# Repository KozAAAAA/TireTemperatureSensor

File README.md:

# TireTemperatureSensor
This is the STM32 board which sends the data collected from the IR Sensor through the CAN bus.

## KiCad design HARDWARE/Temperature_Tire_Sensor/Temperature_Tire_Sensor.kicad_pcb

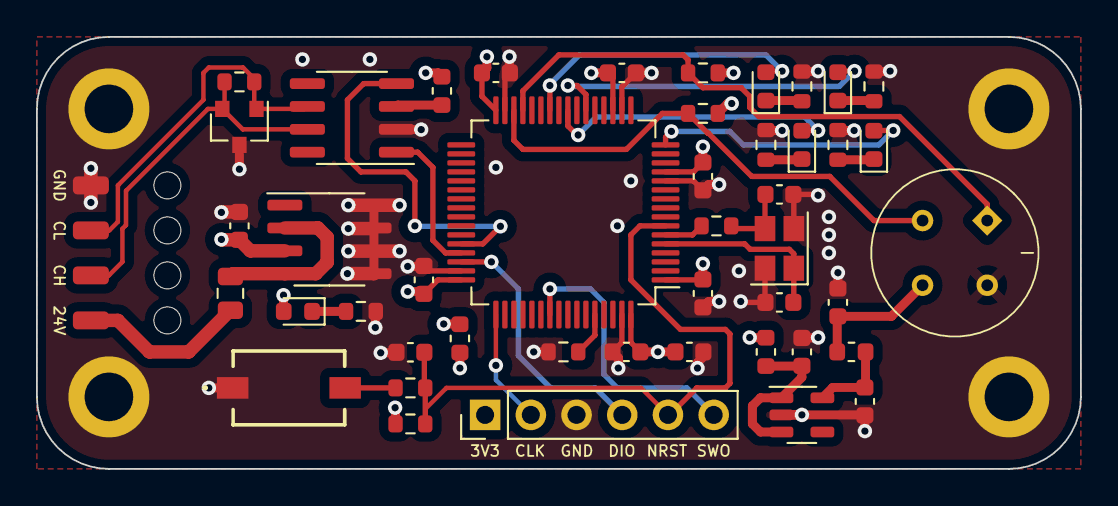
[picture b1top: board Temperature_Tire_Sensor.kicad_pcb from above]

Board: 4 copper layers, 58.0 x 24.0 mm, 50 parts (0 on the bottom side), 33 nets.

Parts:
C1: 0.1u; C_0603_1608Metric
C2: 4u7; C_0603_1608Metric
C3, C4, C6, C8, C9, C10, C11, C12, C14: 100n; C_0603_1608Metric
C5, C7: 8p; C_0603_1608Metric
C13: 10u <3.4Ohm; C_0603_1608Metric
D1, D6: RED; D_0603_1608Metric
D2: PESD2CAN,215; SOT-23
D3, D4: YELLOW; D_0603_1608Metric
D5: GREEN; D_0603_1608Metric
F1: Polyfuse; Fuse_0805_2012Metric
FB1, FB2, FB3, FB4: 60R@100MHz; L_0603_1608Metric
H1, H2, H3, H4: Mounting_Pad; MountingHole_2.7mm_M2.5_ISO14580_Pad
IC1: MLX90621ESF-BAB-000-SP; MLX90621ESFBAB000SP
J1: SWD_01x06; PinHeader_1x06_P2.54mm_Vertical
J2: CAN_01x04; SolderWirePad_1x04_SMD_1x2mm
R1: 100k; R_0603_1608Metric
R2, R8, R9, R11, R12: 1k5; R_0603_1608Metric
R3: 1k; R_0603_1608Metric
R4: 47; R_0603_1608Metric
R5, R6: 4k7; R_0603_1608Metric
R7: 120; R_0603_1608Metric
R10: 10k; R_0603_1608Metric
SW1: RESET; 434781025816
U1: STM32L4P5RET6; LQFP-64_10x10mm_P0.5mm
U2: MIC5236; SOIC-8_3.9x4.9mm_P1.27mm
U3: MIC5306-2.6YD5-TR; TSOT-23-5
U4: SN65HVD232; SOIC-8_3.9x4.9mm_P1.27mm
Y1: 16MGHz; Crystal_SMD_SeikoEpson_TSX3225-4Pin_3.2x2.5mm

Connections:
+2V6: C12.1, FB3.1, U3.5 (VOUT)
+3V3: C13.1, D6.2 (A), FB1.1, FB2.1, FB4.1, J1.1, R5.1, R6.1, R10.2, U2.3 (OUT)
+24V: F1.1, J2.1
/+3V3_uC: C2.1, C3.1, C4.1, C6.1, C8.1, C9.1, C10.1, FB1.2, U1.1 (VBAT), U1.13 (VDDA/VREF+), U1.19 (VDD), U1.32 (VDD), U1.48 (VDDUSB), U1.64 (VDD)
/CAN_H: D2.2 (K), J2.2, R7.1, U4.7 (CANH)
/CAN_L: D2.1 (K), J2.3, R7.2, U4.6 (CANL)
/CAN_RX: U1.44 (PA11), U4.4 (R)
/CAN_TX: U1.45 (PA12), U4.1 (D)
/LED_ERR: D1.2 (A), U1.22 (PA6)
/LED_OK: D5.2 (A), U1.26 (PB0)
/LED_WAR1: D3.2 (A), U1.24 (PC4)
/LED_WAR2: D4.2 (A), U1.16 (PA2)
/NRST: C1.1, J1.5, R3.2, R10.1, U1.7 (NRST)
/OSC_IN: C5.1, U1.5 (PH0-OSC_IN), Y1.1
/OSC_OUT: R4.1, U1.6 (PH1-OSC_OUT)
/SCL: IC1.1 (SCL), R6.2, U1.29 (PB10)
/SDA: IC1.2 (SDA), R5.2, U1.30 (PB11)
/SWCLK: J1.2, U1.49 (PA14)
/SWDIO: J1.4, U1.46 (PA13)
/SWO: J1.6, U1.55 (PB3)
GND: C1.2, C2.2, C3.2, C4.2, C5.2, C6.2, C7.2, C8.2, C9.2, C10.2, C11.2, C12.2, C13.2, C14.2, D2.3 (A), H1.1, H2.1, H3.1, H4.1, IC1.4 (GND), J1.3, J2.4, R1.2, R2.2, R8.2, R9.2, R11.2, R12.2, SW1.1, U1.12 (VSSA/VREF-), U1.18 (VSS), U1.31 (VSS), U1.47 (VSS), U1.63 (VSS), U2.5 (GND), U2.6 (GND), U2.7 (GND), U2.8 (GND), U3.2 (GND), U4.2 (GND), Y1.2, Y1.4
unnamed: C7.1, R4.2, Y1.3
unnamed: C11.1, FB2.2, U3.1 (VIN), U3.3 (EN)
unnamed: C14.1, FB3.2, IC1.3 (VDD)
unnamed: D1.1 (K), R2.1
unnamed: D3.1 (K), R8.1
unnamed: D4.1 (K), R9.1
unnamed: D5.1 (K), R11.1
unnamed: D6.1 (K), R12.1
unnamed: F1.2, U2.2 (IN), U2.4 (EN)
unnamed: FB4.2, U4.3 (VCC)
unnamed: R1.1, U1.60 (PH3-BOOT)
unnamed: R3.1, SW1.2

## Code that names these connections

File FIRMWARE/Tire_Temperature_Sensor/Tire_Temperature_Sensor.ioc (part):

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Mcu.Name=STM32L4P5R(G-E)Tx
Mcu.Package=LQFP64
Mcu.UserName=STM32L4P5RETx
PA11.Mode=CAN_Activate
PA11.Signal=CAN1_RX
PA12.Mode=CAN_Activate
PA12.Signal=CAN1_TX
PA13\ (JTMS/SWDIO).Mode=Trace_Asynchronous_SW
PA13\ (JTMS/SWDIO).Signal=SYS_JTMS-SWDIO
PA14\ (JTCK/SWCLK).Mode=Trace_Asynchronous_SW
PA14\ (JTCK/SWCLK).Signal=SYS_JTCK-SWCLK
PA2.GPIOParameters=GPIO_Label
PA2.GPIO_Label=LED_WAR2
PA2.Signal=GPIO_Output
PA6.GPIOParameters=GPIO_Label
PA6.GPIO_Label=LED_ERR
PA6.Signal=GPIO_Output
PB0.GPIOParameters=GPIO_Label
PB0.GPIO_Label=LED_OK
PB0.Signal=GPIO_Output
PB10.Mode=I2C
PB10.Signal=I2C2_SCL
PB11.Mode=I2C
PB11.Signal=I2C2_SDA
PB3\ (JTDO/TRACESWO).Mode=Trace_Asynchronous_SW
PB3\ (JTDO/TRACESWO).Signal=SYS_JTDO-SWO
PC4.GPIOParameters=GPIO_Label
PC4.GPIO_Label=LED_WAR1
PC4.Signal=GPIO_Output
PH0-OSC_IN\ (PH0).Mode=HSE-External-Oscillator
PH0-OSC_IN\ (PH0).Signal=RCC_OSC_IN
PH1-OSC_OUT\ (PH1).Mode=HSE-External-Oscillator
PH1-OSC_OUT\ (PH1).Signal=RCC_OSC_OUT
RCC.HSE_VALUE=16000000
RCC.SYSCLKFreq_VALUE=120000000
RCC.SYSCLKSource=RCC_SYSCLKSOURCE_PLLCLK
board=custom

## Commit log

2022-05-03 First commit - the Stm32 configuration and uncompleted schematic
2022-05-03 Readme.md
2022-05-11 A completed schematic
2022-05-12 Changed the used type of labels and added power flags
2022-05-15 Added all of the footprints
2022-05-17 pcb layout half done
2022-05-18 pcb layout done - waiting for the confirmation of layout V1
2022-05-23 Power planes has been added
2022-05-24 Routing mostly done - GND and 3V3_uC vias have to be added
2022-05-25 Completed the routing
2022-05-26 A completed V1.0 of the board
2022-05-26 readme update
2022-06-14 Added some vias, changed the silkscreen, added some GND planes
2022-06-14 merge
2022-07-22 LED blink setup & basic code
2022-07-22 mlx library has been added
2022-07-22 EEProm read has been ported to HAL - not checked yet
2022-07-23 Driver has been written - not checked yet
2022-07-24 error handling
2022-07-24 EEProp read works, I2CRead doesn't
2022-07-26 mem_read custom functions
2022-07-26 I2C driver works (I think so)
2022-07-26 Init works - functions has been tested
2022-07-26 Request_Mem_Read optimised
2022-07-26 Ta read works
2022-07-26 To read works <3
2022-07-27 3D files
2022-07-28 Average temperature array
2022-07-28 Can lib added
2022-07-30 save before Can tests
2022-08-02 loopback works
2022-08-02 working can
2022-08-02 PUTM CAN LIB WORKS
